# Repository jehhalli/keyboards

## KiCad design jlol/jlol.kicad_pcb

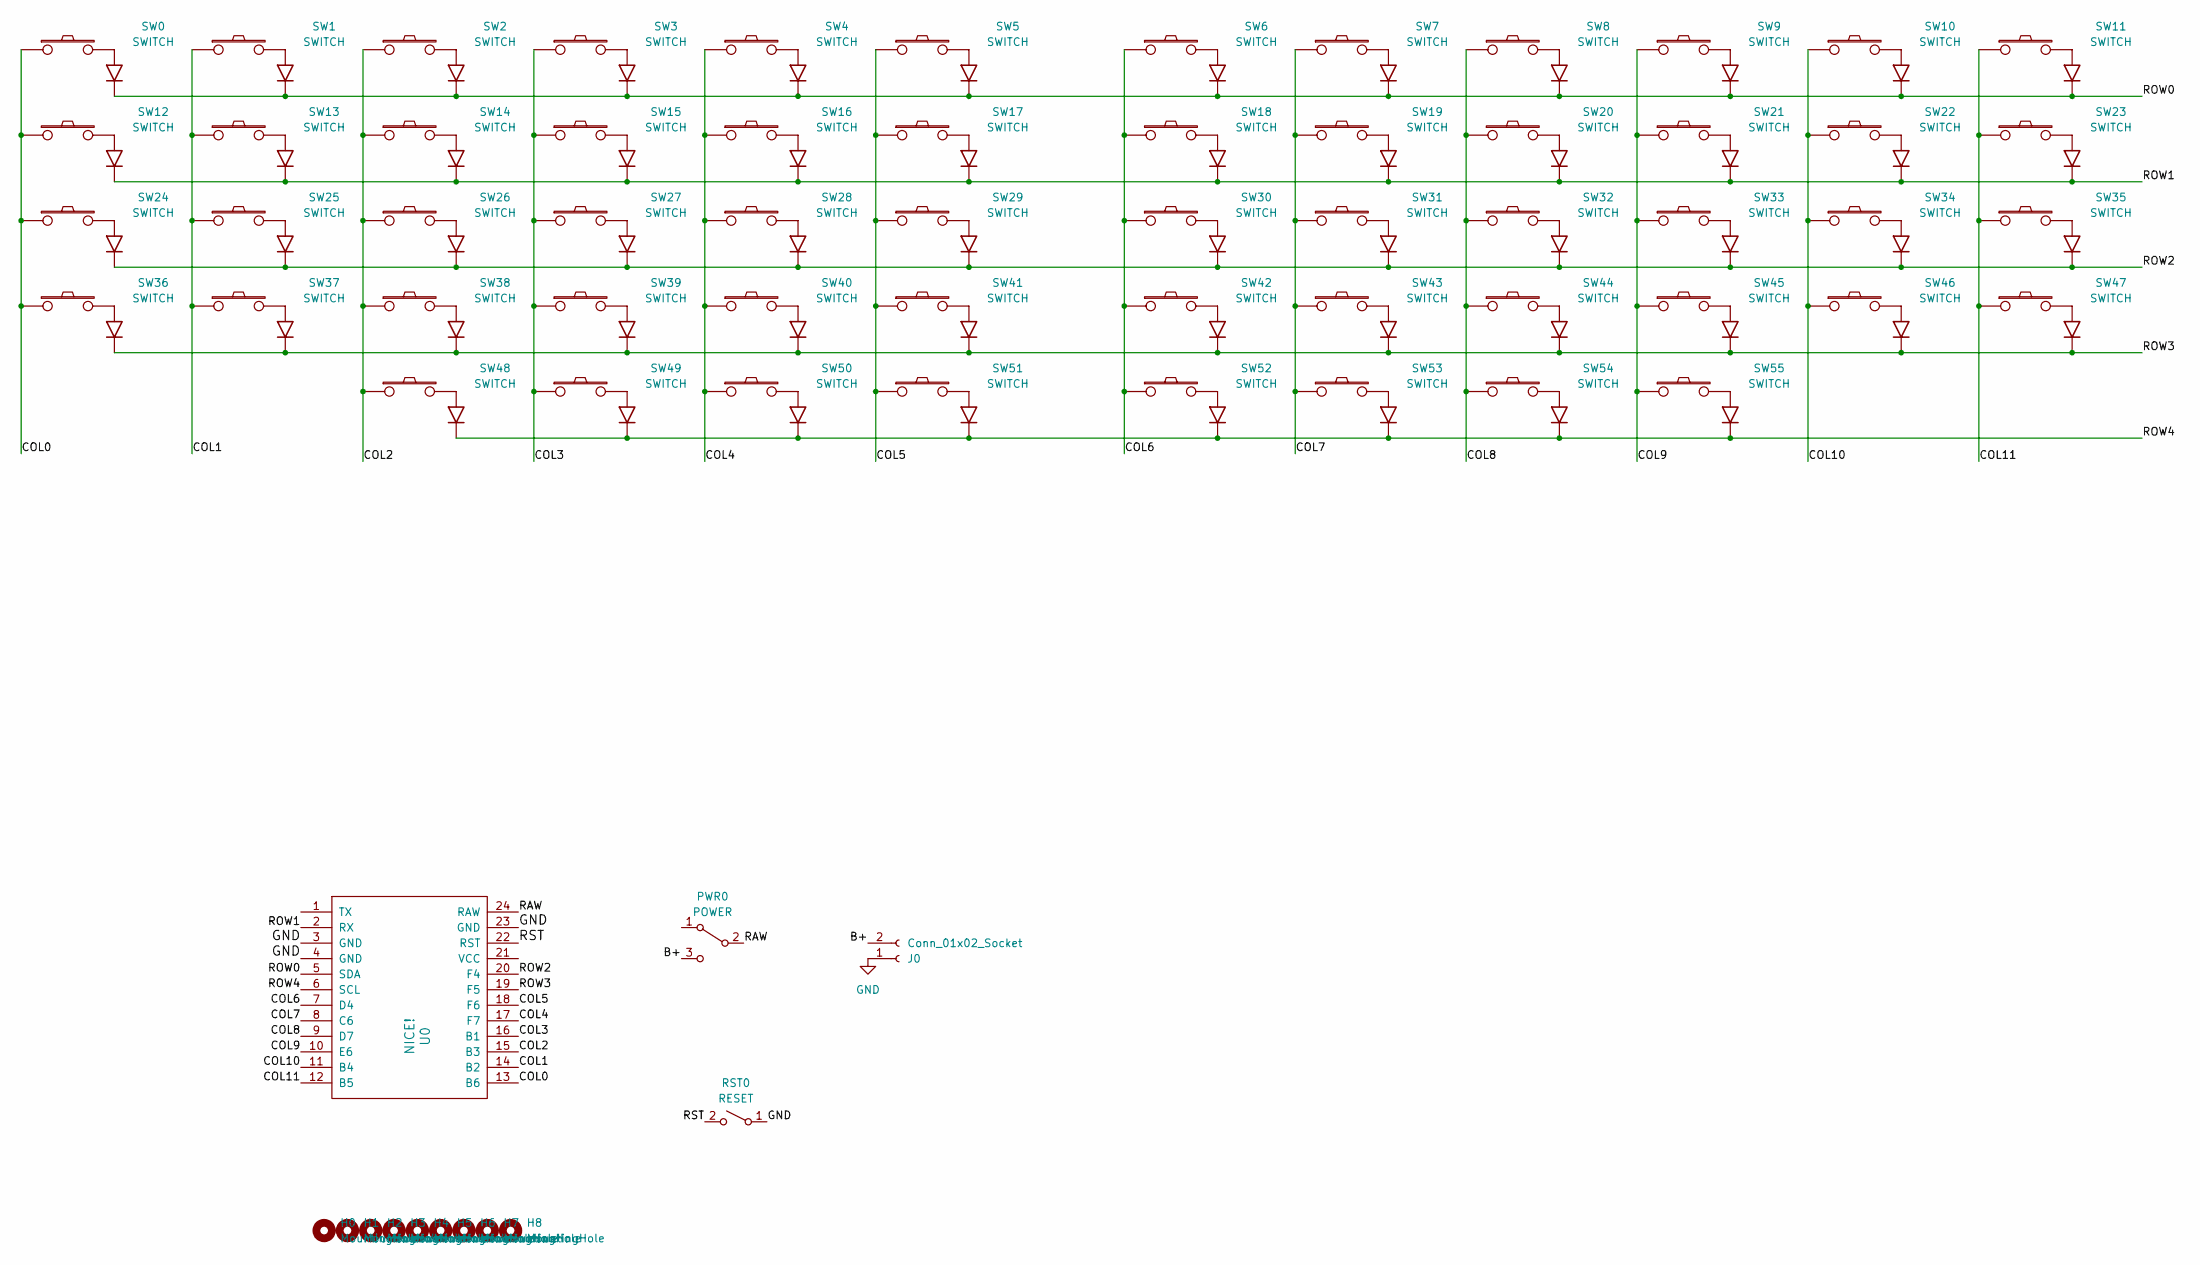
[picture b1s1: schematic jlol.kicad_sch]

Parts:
H0, H1, H2, H3, H4, H5, H6, H7, H8: MountingHole; MountingHole_3.5mm
J0: Conn_01x02_Socket; jst_ph
PWR0: POWER; power_switch_1
RST0: RESET; reset_button
SW0, SW1, SW2, SW3, SW4, SW5, SW6, SW7, SW8, SW9, SW10, SW11, SW12, SW13, SW14, SW15, SW16, SW17, SW18, SW19, SW20, SW21, SW22, SW23, SW24, SW25, SW26, SW27, SW28, SW29, SW30, SW31, SW32, SW33, SW34, SW35, SW36, SW37, SW38, SW39, SW40, SW41, SW42, SW43, SW44, SW45, SW46, SW47, SW48, SW49, SW50, SW51, SW52, SW53, SW54, SW55: SWITCH; cherry_hotswap_with_thru_diode
U0: NICE!; nice!nano

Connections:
/B+: J0.2, PWR0.3 (C)
/COL0: SW0.1, SW12.1, SW24.1, SW36.1, U0.13 (B6)
/COL1: SW1.1, SW13.1, SW25.1, SW37.1, U0.14 (B2)
/COL2: SW2.1, SW14.1, SW26.1, SW38.1, SW48.1, U0.15 (B3)
/COL3: SW3.1, SW15.1, SW27.1, SW39.1, SW49.1, U0.16 (B1)
/COL4: SW4.1, SW16.1, SW28.1, SW40.1, SW50.1, U0.17 (F7)
/COL5: SW5.1, SW17.1, SW29.1, SW41.1, SW51.1, U0.18 (F6)
/COL6: SW6.1, SW18.1, SW30.1, SW42.1, SW52.1, U0.7 (D4)
/COL7: SW7.1, SW19.1, SW31.1, SW43.1, SW53.1, U0.8 (C6)
/COL8: SW8.1, SW20.1, SW32.1, SW44.1, SW54.1, U0.9 (D7)
/COL9: SW9.1, SW21.1, SW33.1, SW45.1, SW55.1, U0.10 (E6)
/COL10: SW10.1, SW22.1, SW34.1, SW46.1, U0.11 (B4)
/COL11: SW11.1, SW23.1, SW35.1, SW47.1, U0.12 (B5)
/RAW: PWR0.2 (B), U0.24 (RAW)
/ROW0: SW0.3 (K), SW1.3 (K), SW2.3 (K), SW3.3 (K), SW4.3 (K), SW5.3 (K), SW6.3 (K), SW7.3 (K), SW8.3 (K), SW9.3 (K), SW10.3 (K), SW11.3 (K), U0.5 (SDA)
/ROW1: SW12.3 (K), SW13.3 (K), SW14.3 (K), SW15.3 (K), SW16.3 (K), SW17.3 (K), SW18.3 (K), SW19.3 (K), SW20.3 (K), SW21.3 (K), SW22.3 (K), SW23.3 (K), U0.2 (RX)
/ROW2: SW24.3 (K), SW25.3 (K), SW26.3 (K), SW27.3 (K), SW28.3 (K), SW29.3 (K), SW30.3 (K), SW31.3 (K), SW32.3 (K), SW33.3 (K), SW34.3 (K), SW35.3 (K), U0.20 (F4)
/ROW3: SW36.3 (K), SW37.3 (K), SW38.3 (K), SW39.3 (K), SW40.3 (K), SW41.3 (K), SW42.3 (K), SW43.3 (K), SW44.3 (K), SW45.3 (K), SW46.3 (K), SW47.3 (K), U0.19 (F5)
/ROW4: SW48.3 (K), SW49.3 (K), SW50.3 (K), SW51.3 (K), SW52.3 (K), SW53.3 (K), SW54.3 (K), SW55.3 (K), U0.6 (SCL)
/RST: RST0.2 (B), U0.22 (RST)
GND: J0.1, RST0.1 (A), U0.3 (GND), U0.4 (GND), U0.23 (GND)

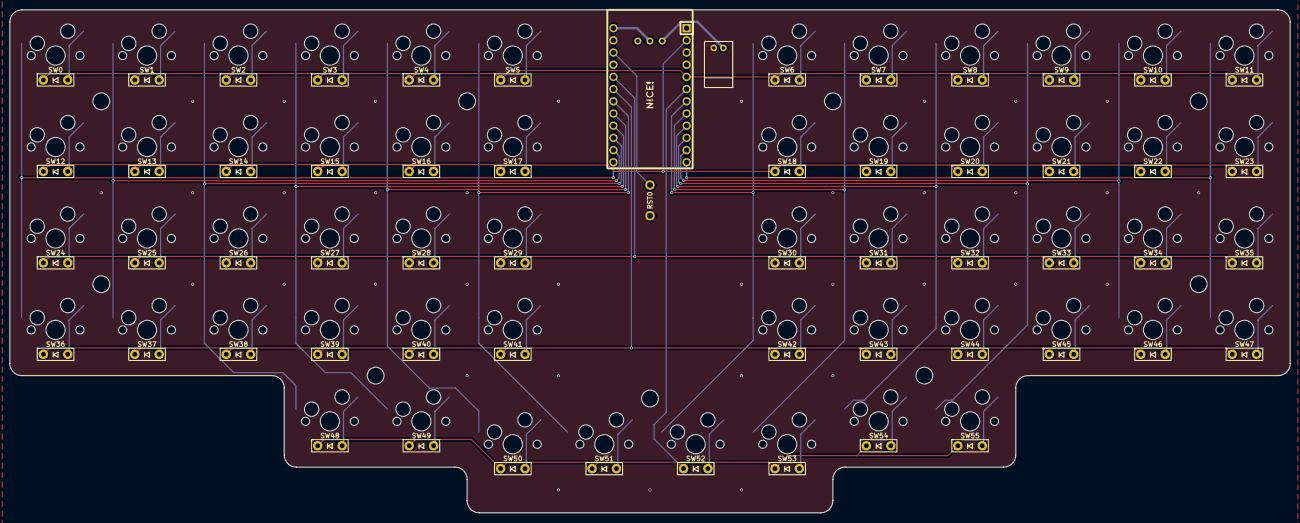
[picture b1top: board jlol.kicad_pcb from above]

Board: 2 copper layers, 266.7 x 104.8 mm, 69 parts (1 on the bottom side), 21 nets.

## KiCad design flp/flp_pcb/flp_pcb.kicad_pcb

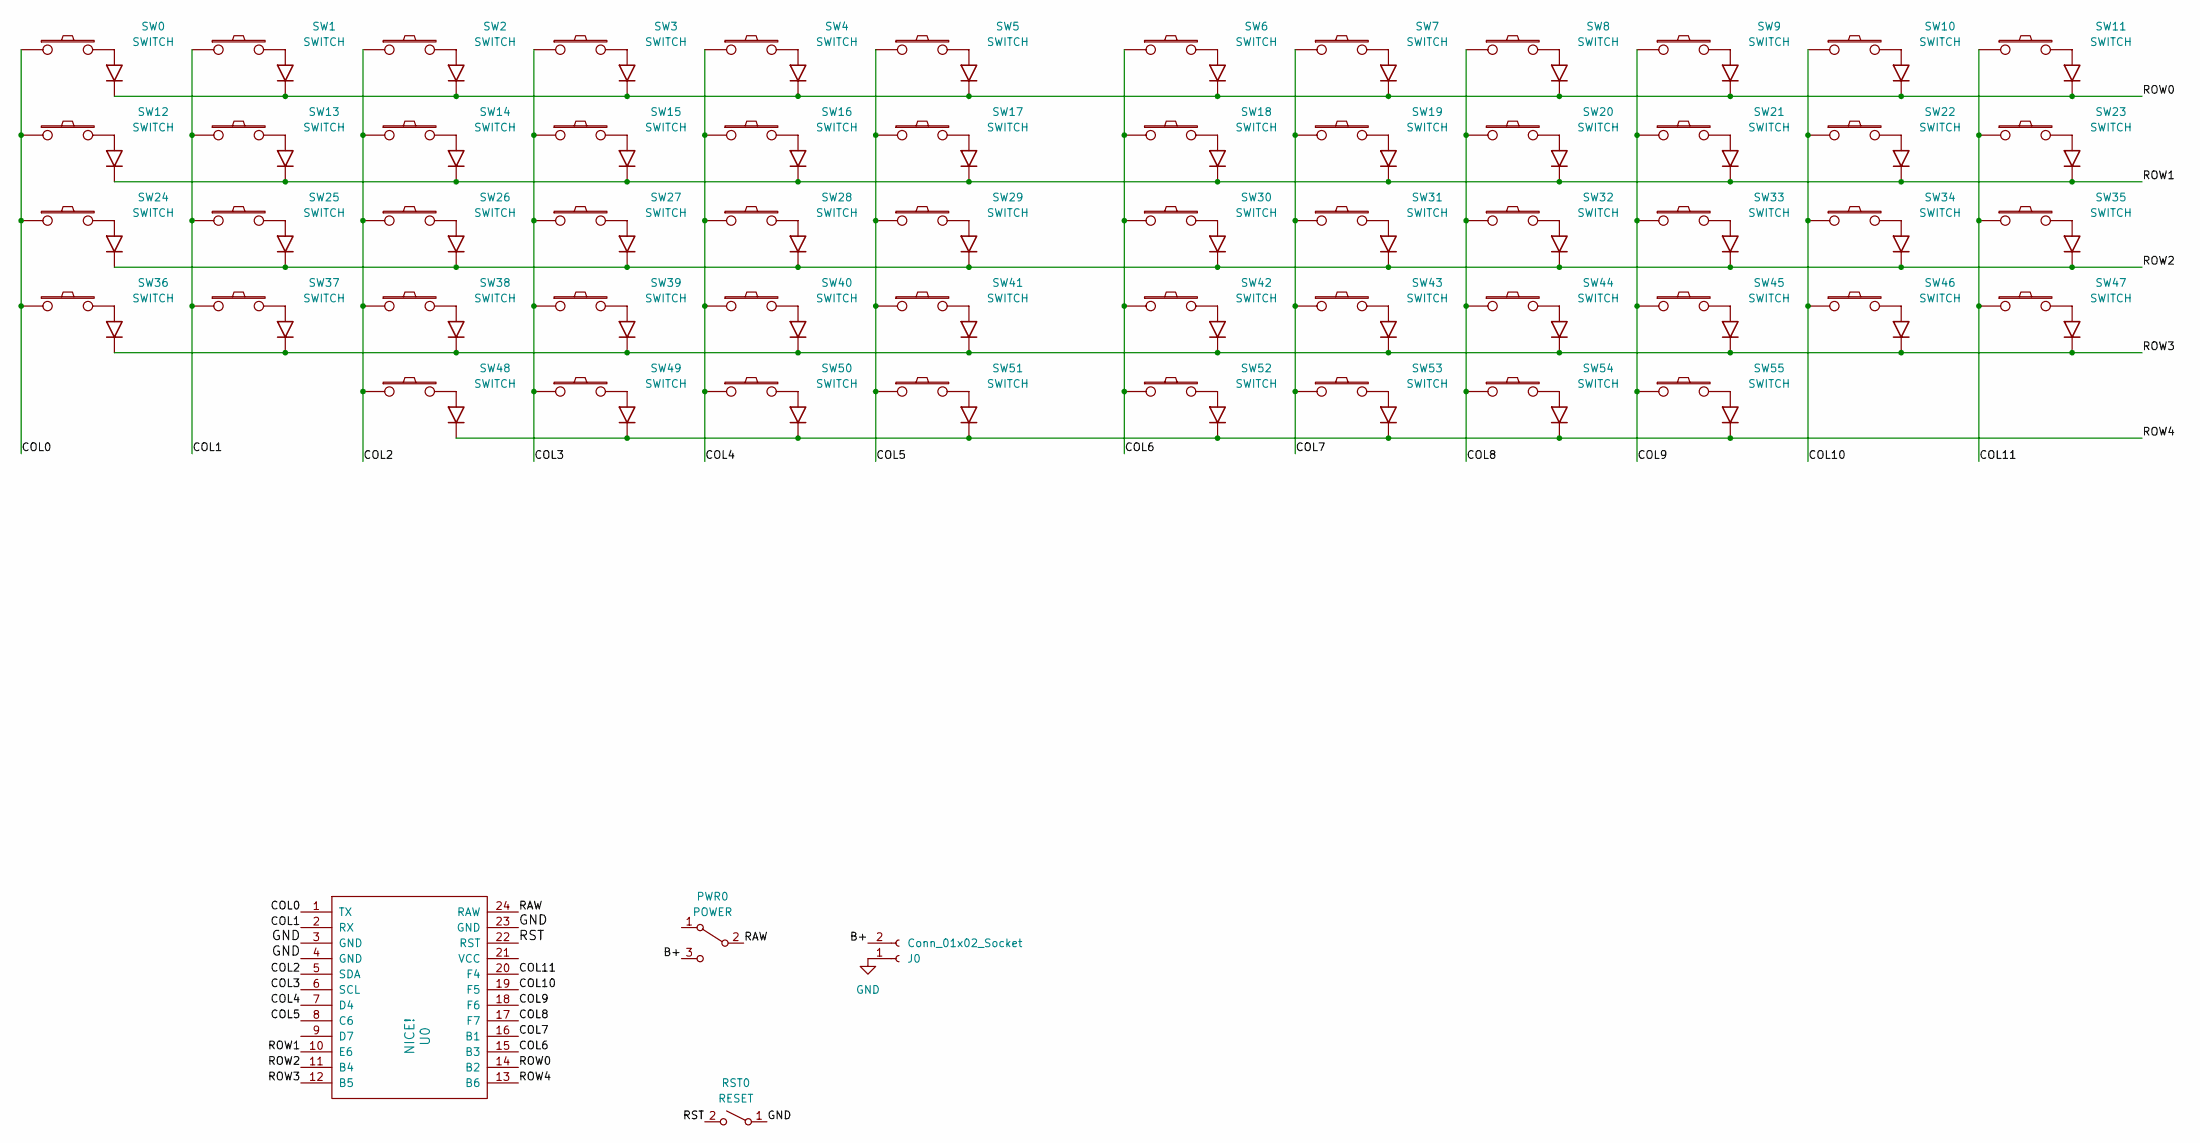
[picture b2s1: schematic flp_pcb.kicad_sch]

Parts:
J0: Conn_01x02_Socket; SolderWire-1sqmm_1x02_P5.4mm_D1.4mm_OD2.7mm
PWR0: POWER; power_switch_1
RST0: RESET; cherry_hotswap
SW0, SW1, SW2, SW3, SW4, SW5, SW6, SW7, SW8, SW9, SW10, SW11, SW12, SW13, SW14, SW15, SW16, SW17, SW18, SW19, SW20, SW21, SW22, SW23, SW24, SW25, SW26, SW27, SW28, SW29, SW30, SW31, SW32, SW33, SW34, SW35, SW36, SW37, SW38, SW39, SW40, SW41, SW42, SW43, SW44, SW45, SW46, SW47, SW48, SW49, SW50, SW51, SW52, SW53, SW54, SW55: SWITCH; kailh_choc_with_diode
U0: NICE!; pro_micro_castellated

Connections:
/B+: J0.2, PWR0.3 (C)
/COL0: SW0.1, SW12.1, SW24.1, SW36.1, U0.1 (TX)
/COL1: SW1.1, SW13.1, SW25.1, SW37.1, U0.2 (RX)
/COL2: SW2.1, SW14.1, SW26.1, SW38.1, SW48.1, U0.5 (SDA)
/COL3: SW3.1, SW15.1, SW27.1, SW39.1, SW49.1, U0.6 (SCL)
/COL4: SW4.1, SW16.1, SW28.1, SW40.1, SW50.1, U0.7 (D4)
/COL5: SW5.1, SW17.1, SW29.1, SW41.1, SW51.1, U0.8 (C6)
/COL6: SW6.1, SW18.1, SW30.1, SW42.1, SW52.1, U0.15 (B3)
/COL7: SW7.1, SW19.1, SW31.1, SW43.1, SW53.1, U0.16 (B1)
/COL8: SW8.1, SW20.1, SW32.1, SW44.1, SW54.1, U0.17 (F7)
/COL9: SW9.1, SW21.1, SW33.1, SW45.1, SW55.1, U0.18 (F6)
/COL10: SW10.1, SW22.1, SW34.1, SW46.1, U0.19 (F5)
/COL11: SW11.1, SW23.1, SW35.1, SW47.1, U0.20 (F4)
/RAW: PWR0.2 (B), U0.24 (RAW)
/ROW0: SW0.3 (K), SW1.3 (K), SW2.3 (K), SW3.3 (K), SW4.3 (K), SW5.3 (K), SW6.3 (K), SW7.3 (K), SW8.3 (K), SW9.3 (K), SW10.3 (K), SW11.3 (K), U0.14 (B2)
/ROW1: SW12.3 (K), SW13.3 (K), SW14.3 (K), SW15.3 (K), SW16.3 (K), SW17.3 (K), SW18.3 (K), SW19.3 (K), SW20.3 (K), SW21.3 (K), SW22.3 (K), SW23.3 (K), U0.10 (E6)
/ROW2: SW24.3 (K), SW25.3 (K), SW26.3 (K), SW27.3 (K), SW28.3 (K), SW29.3 (K), SW30.3 (K), SW31.3 (K), SW32.3 (K), SW33.3 (K), SW34.3 (K), SW35.3 (K), U0.11 (B4)
/ROW3: SW36.3 (K), SW37.3 (K), SW38.3 (K), SW39.3 (K), SW40.3 (K), SW41.3 (K), SW42.3 (K), SW43.3 (K), SW44.3 (K), SW45.3 (K), SW46.3 (K), SW47.3 (K), U0.12 (B5)
/ROW4: SW48.3 (K), SW49.3 (K), SW50.3 (K), SW51.3 (K), SW52.3 (K), SW53.3 (K), SW54.3 (K), SW55.3 (K), U0.13 (B6)
/RST: RST0.2 (B), U0.22 (RST)
GND: J0.1, RST0.1 (A), U0.3 (GND), U0.4 (GND), U0.23 (GND)

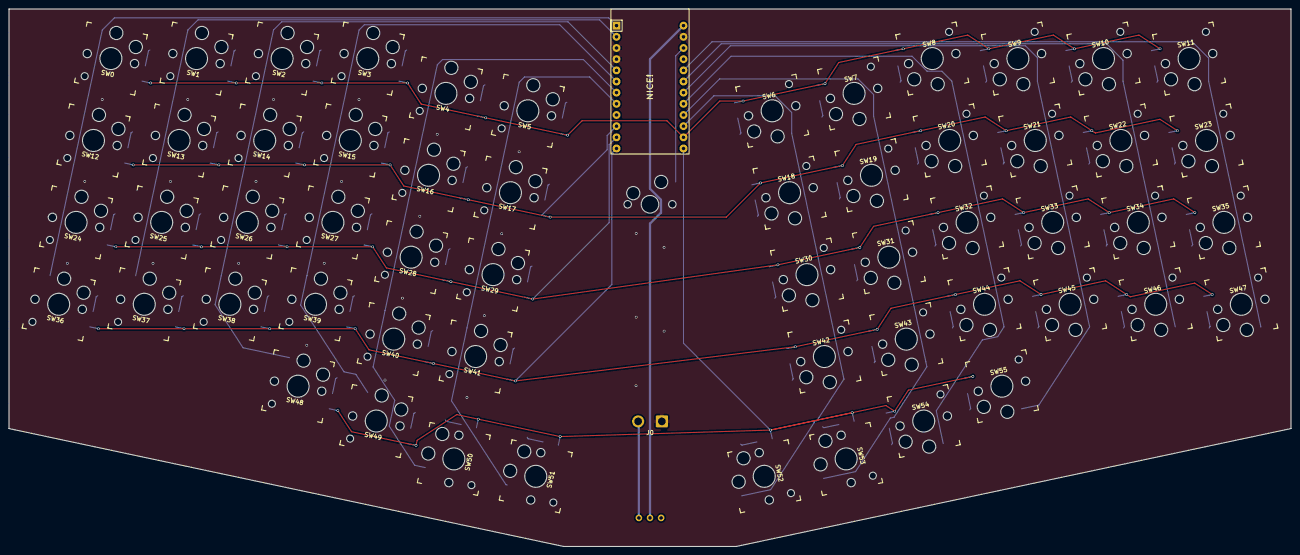
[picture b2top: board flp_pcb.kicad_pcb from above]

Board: 2 copper layers, 291.6 x 122.3 mm, 60 parts (0 on the bottom side), 21 nets.

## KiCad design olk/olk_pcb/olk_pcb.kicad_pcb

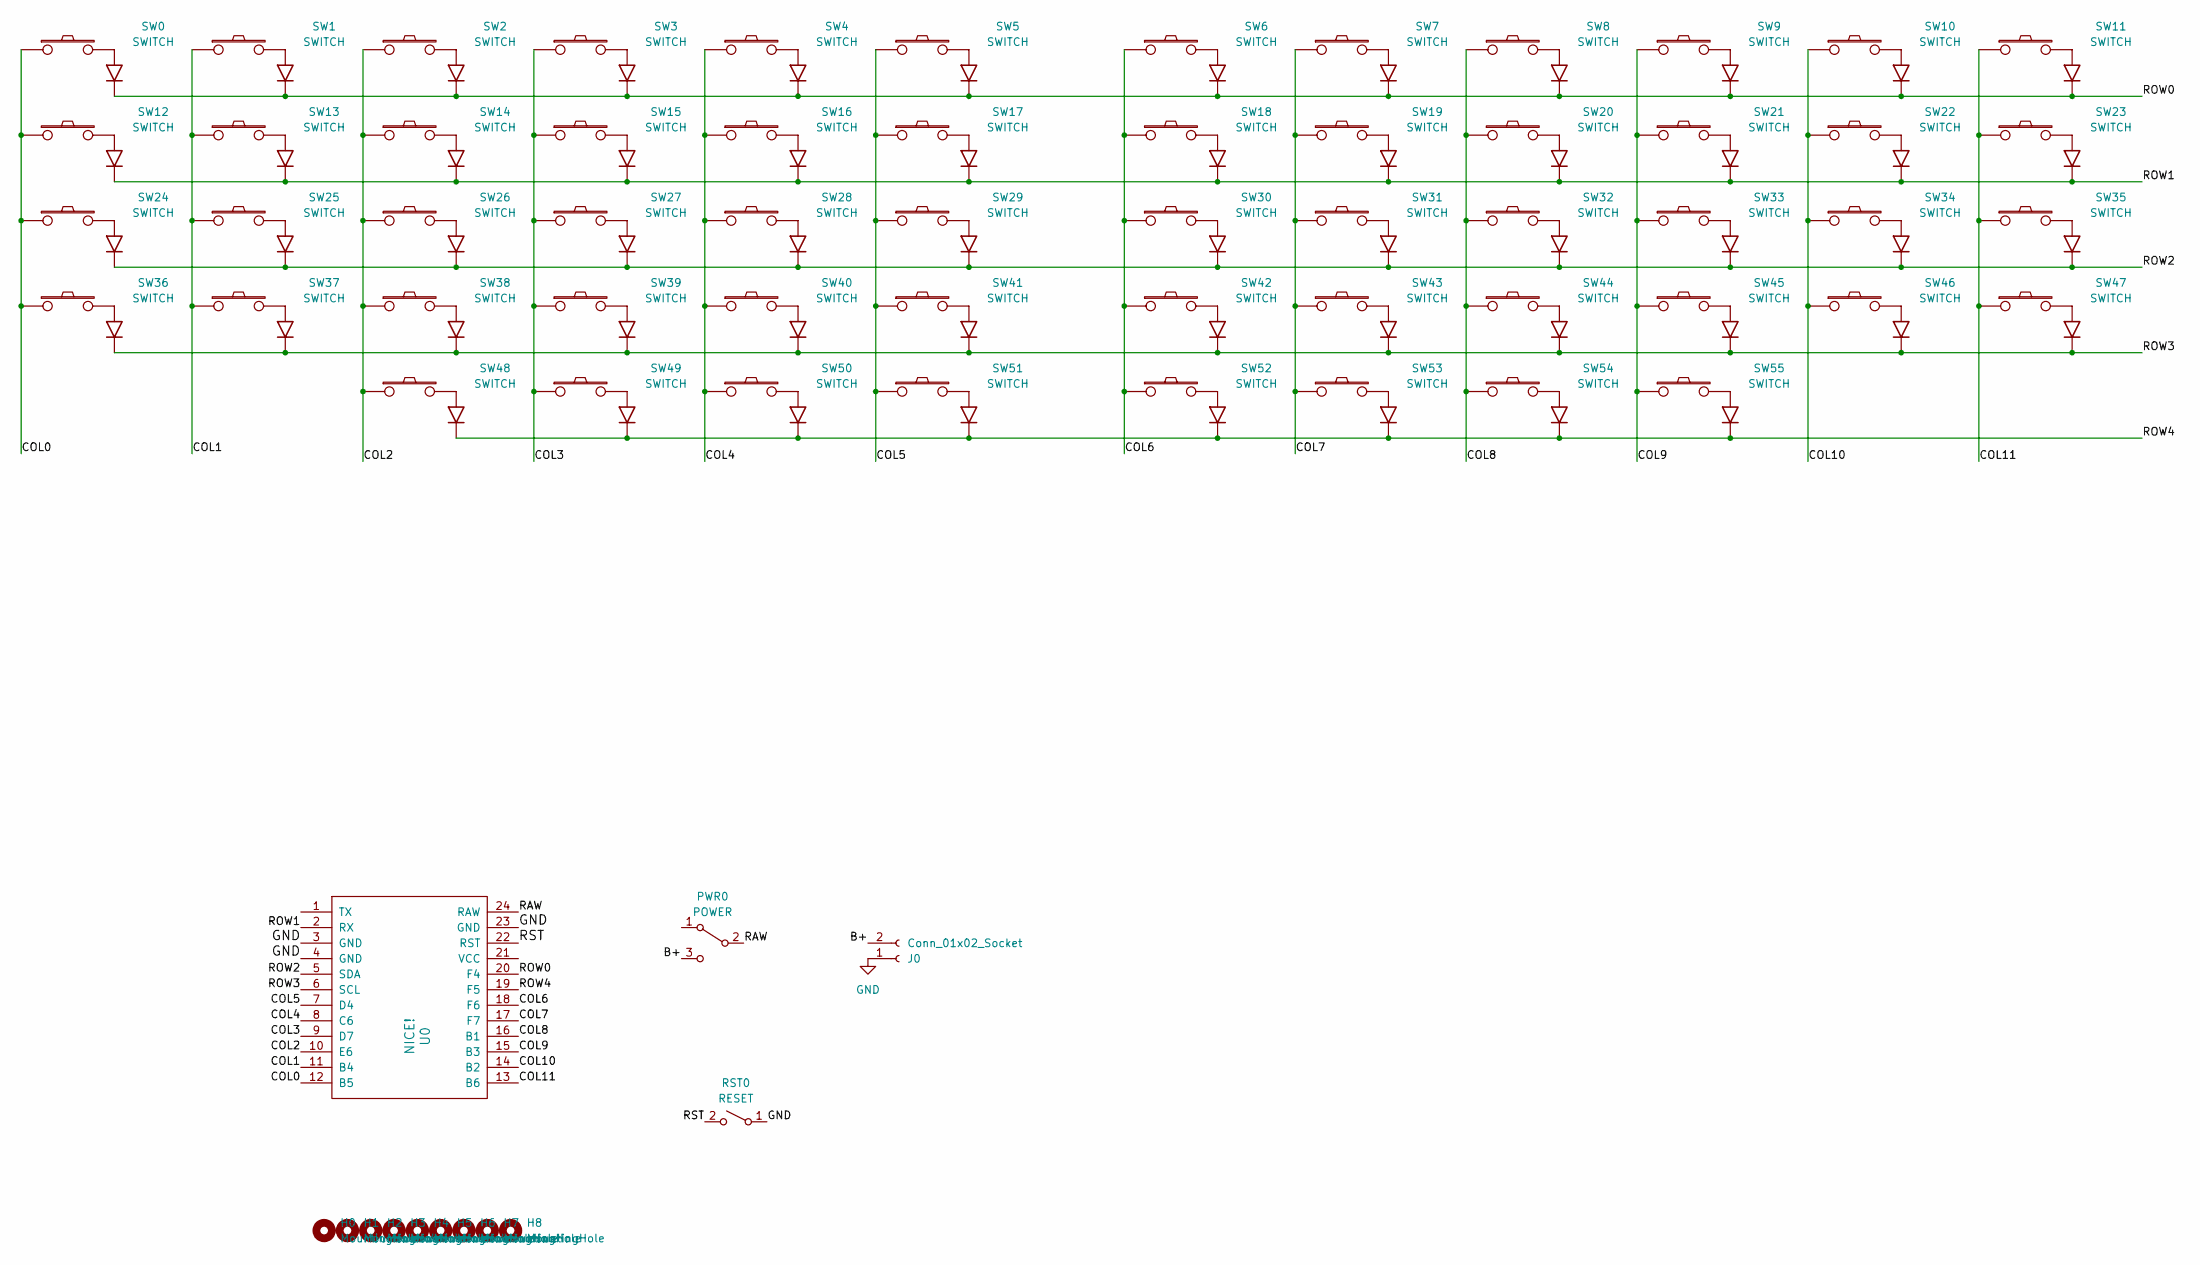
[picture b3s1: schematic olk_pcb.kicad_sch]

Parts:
H0, H1, H2, H3, H4, H5, H6, H7, H8: MountingHole; MountingHole_3.5mm
J0: Conn_01x02_Socket; PinHeader_1x02_P2.54mm_Vertical
PWR0: POWER; power_switch_1
RST0: RESET; reset_button
SW0, SW1, SW2, SW3, SW4, SW5, SW6, SW7, SW8, SW9, SW10, SW11, SW12, SW13, SW14, SW15, SW16, SW17, SW18, SW19, SW20, SW21, SW22, SW23, SW24, SW25, SW26, SW27, SW28, SW29, SW30, SW31, SW32, SW33, SW34, SW35, SW36, SW37, SW38, SW39, SW40, SW41, SW42, SW43, SW44, SW45, SW46, SW47, SW48, SW49, SW50, SW51, SW52, SW53, SW54, SW55: SWITCH; cherry_hotswap_with_diode
U0: NICE!; pro_micro_castellated

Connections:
/B+: J0.2, PWR0.3 (C)
/COL0: SW0.1, SW12.1, SW24.1, SW36.1, U0.12 (B5)
/COL1: SW1.1, SW13.1, SW25.1, SW37.1, U0.11 (B4)
/COL2: SW2.1, SW14.1, SW26.1, SW38.1, SW48.1, U0.10 (E6)
/COL3: SW3.1, SW15.1, SW27.1, SW39.1, SW49.1, U0.9 (D7)
/COL4: SW4.1, SW16.1, SW28.1, SW40.1, SW50.1, U0.8 (C6)
/COL5: SW5.1, SW17.1, SW29.1, SW41.1, SW51.1, U0.7 (D4)
/COL6: SW6.1, SW18.1, SW30.1, SW42.1, SW52.1, U0.18 (F6)
/COL7: SW7.1, SW19.1, SW31.1, SW43.1, SW53.1, U0.17 (F7)
/COL8: SW8.1, SW20.1, SW32.1, SW44.1, SW54.1, U0.16 (B1)
/COL9: SW9.1, SW21.1, SW33.1, SW45.1, SW55.1, U0.15 (B3)
/COL10: SW10.1, SW22.1, SW34.1, SW46.1, U0.14 (B2)
/COL11: SW11.1, SW23.1, SW35.1, SW47.1, U0.13 (B6)
/RAW: PWR0.2 (B), U0.24 (RAW)
/ROW0: SW0.3 (K), SW1.3 (K), SW2.3 (K), SW3.3 (K), SW4.3 (K), SW5.3 (K), SW6.3 (K), SW7.3 (K), SW8.3 (K), SW9.3 (K), SW10.3 (K), SW11.3 (K), U0.20 (F4)
/ROW1: SW12.3 (K), SW13.3 (K), SW14.3 (K), SW15.3 (K), SW16.3 (K), SW17.3 (K), SW18.3 (K), SW19.3 (K), SW20.3 (K), SW21.3 (K), SW22.3 (K), SW23.3 (K), U0.2 (RX)
/ROW2: SW24.3 (K), SW25.3 (K), SW26.3 (K), SW27.3 (K), SW28.3 (K), SW29.3 (K), SW30.3 (K), SW31.3 (K), SW32.3 (K), SW33.3 (K), SW34.3 (K), SW35.3 (K), U0.5 (SDA)
/ROW3: SW36.3 (K), SW37.3 (K), SW38.3 (K), SW39.3 (K), SW40.3 (K), SW41.3 (K), SW42.3 (K), SW43.3 (K), SW44.3 (K), SW45.3 (K), SW46.3 (K), SW47.3 (K), U0.6 (SCL)
/ROW4: SW48.3 (K), SW49.3 (K), SW50.3 (K), SW51.3 (K), SW52.3 (K), SW53.3 (K), SW54.3 (K), SW55.3 (K), U0.19 (F5)
/RST: RST0.2 (B), U0.22 (RST)
GND: J0.1, RST0.1 (A), U0.3 (GND), U0.4 (GND), U0.23 (GND)

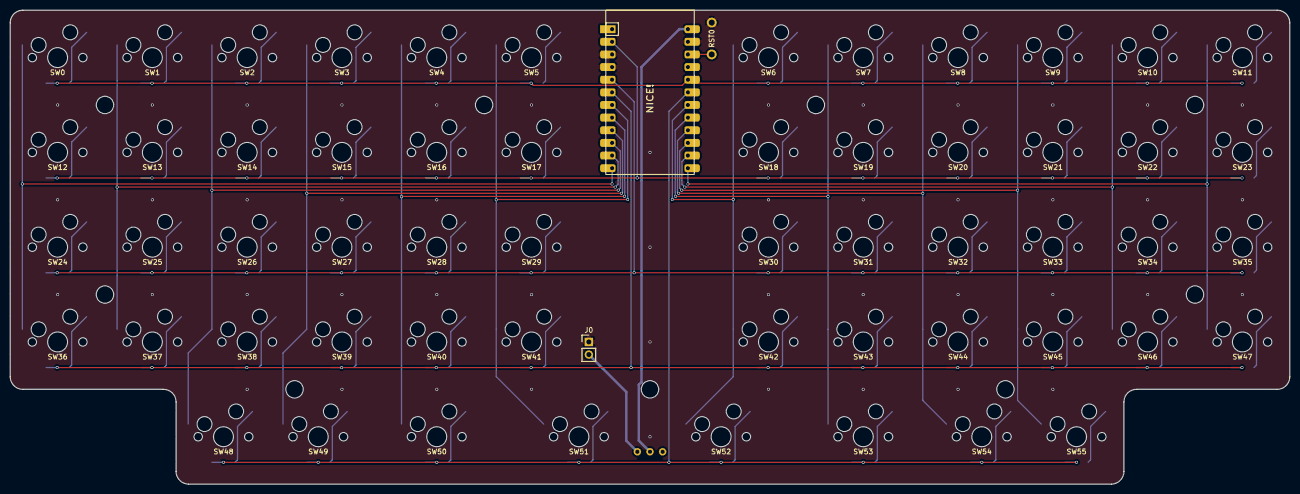
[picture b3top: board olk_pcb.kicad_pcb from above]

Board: 2 copper layers, 257.2 x 95.2 mm, 69 parts (0 on the bottom side), 21 nets.

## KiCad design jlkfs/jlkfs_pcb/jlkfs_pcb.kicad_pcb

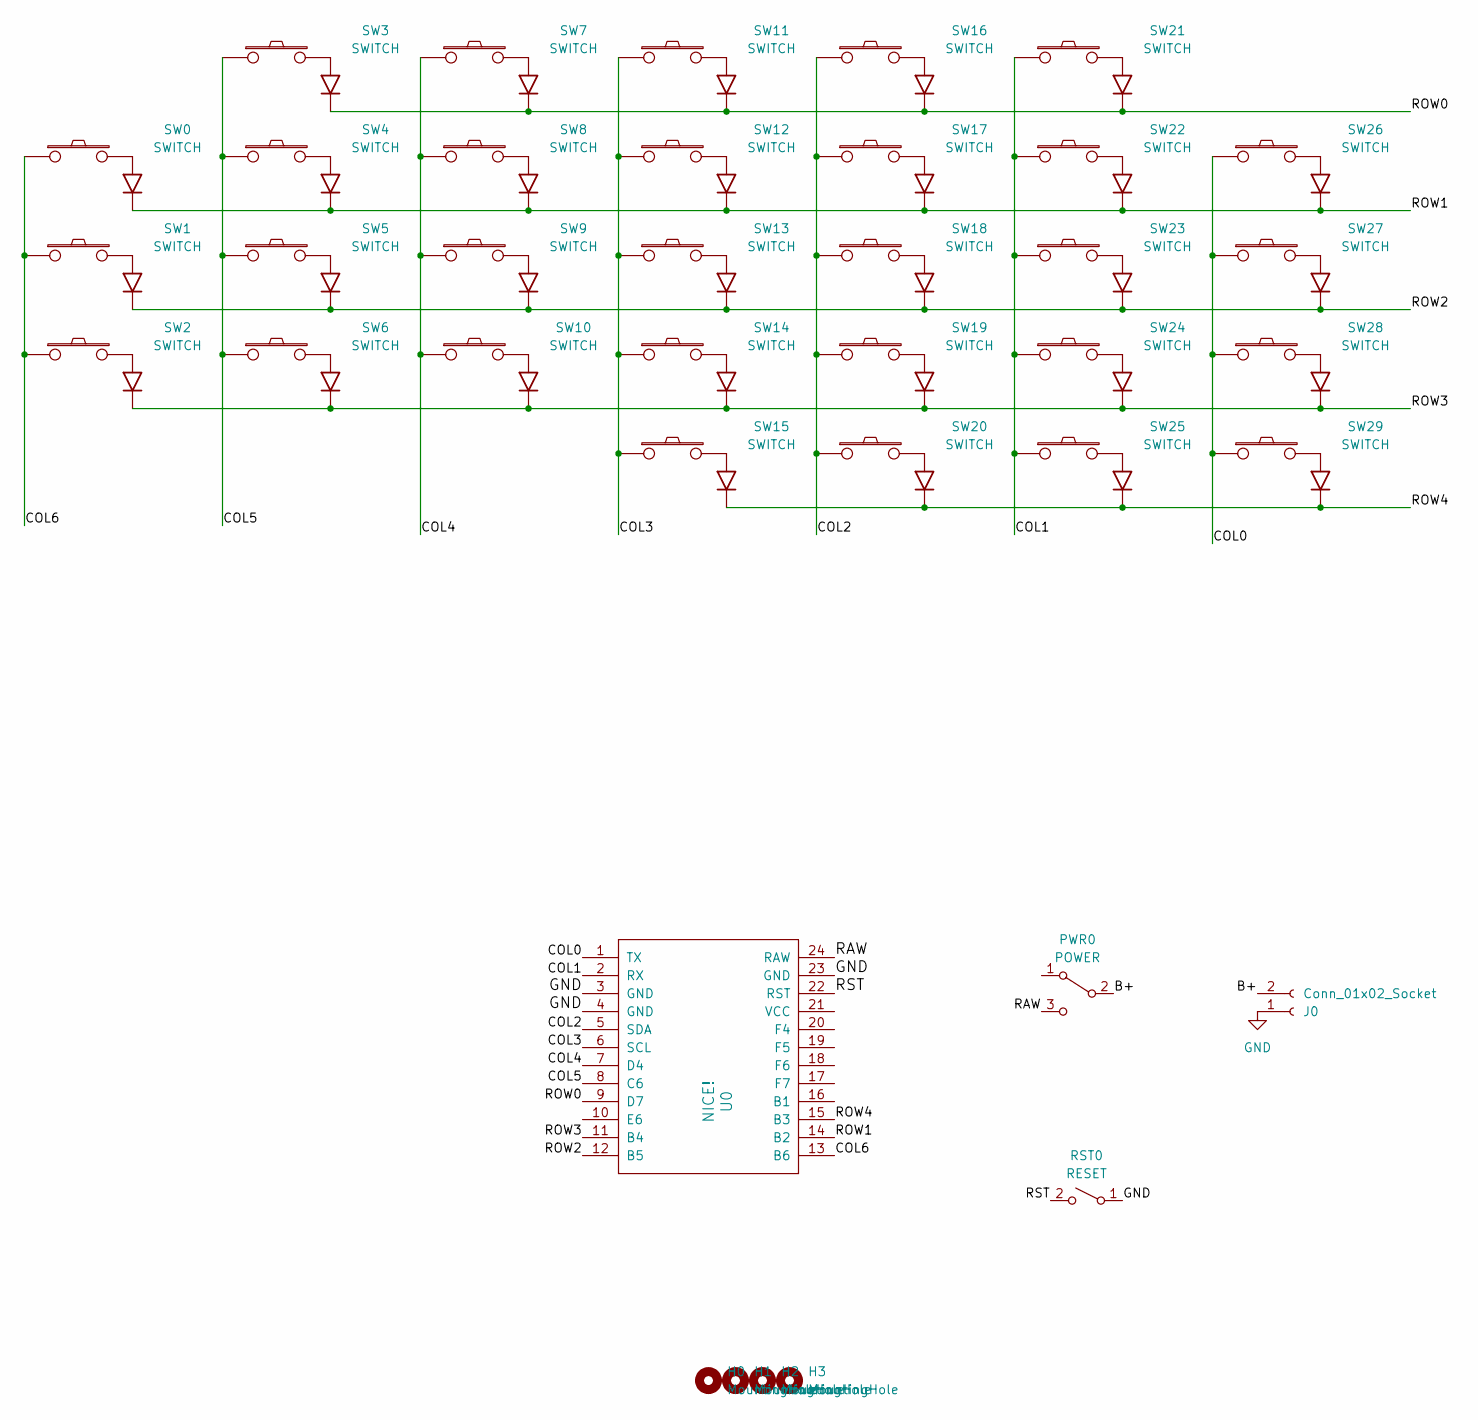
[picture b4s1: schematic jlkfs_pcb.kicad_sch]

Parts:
H0, H1, H2, H3: MountingHole; MountingHole_3.5mm
J0: Conn_01x02_Socket; PinHeader_1x02_P2.54mm_Vertical
PWR0: POWER; power_switch_1
RST0: RESET; reset_button
SW0, SW1, SW2, SW3, SW4, SW5, SW6, SW7, SW8, SW9, SW10, SW11, SW12, SW13, SW14, SW15, SW16, SW17, SW18, SW19, SW20, SW21, SW22, SW23, SW24, SW25, SW26, SW27, SW28, SW29: SWITCH; cherry_hotswap_dual_with_diode
U0: NICE!; nice!nano

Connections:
/B+: J0.2, PWR0.2 (B)
/COL0: SW26.1, SW27.1, SW28.1, SW29.1, U0.1 (TX)
/COL1: SW21.1, SW22.1, SW23.1, SW24.1, SW25.1, U0.2 (RX)
/COL2: SW16.1, SW17.1, SW18.1, SW19.1, SW20.1, U0.5 (SDA)
/COL3: SW11.1, SW12.1, SW13.1, SW14.1, SW15.1, U0.6 (SCL)
/COL4: SW7.1, SW8.1, SW9.1, SW10.1, U0.7 (D4)
/COL5: SW3.1, SW4.1, SW5.1, SW6.1, U0.8 (C6)
/COL6: SW0.1, SW1.1, SW2.1, U0.13 (B6)
/RAW: PWR0.3 (C), U0.24 (RAW)
/ROW0: SW3.3 (K), SW7.3 (K), SW11.3 (K), SW16.3 (K), SW21.3 (K), U0.9 (D7)
/ROW1: SW0.3 (K), SW4.3 (K), SW8.3 (K), SW12.3 (K), SW17.3 (K), SW22.3 (K), SW26.3 (K), U0.14 (B2)
/ROW2: SW1.3 (K), SW5.3 (K), SW9.3 (K), SW13.3 (K), SW18.3 (K), SW23.3 (K), SW27.3 (K), U0.12 (B5)
/ROW3: SW2.3 (K), SW6.3 (K), SW10.3 (K), SW14.3 (K), SW19.3 (K), SW24.3 (K), SW28.3 (K), U0.11 (B4)
/ROW4: SW15.3 (K), SW20.3 (K), SW25.3 (K), SW29.3 (K), U0.15 (B3)
/RST: RST0.2 (B), U0.22 (RST)
GND: J0.1, RST0.1 (A), U0.3 (GND), U0.4 (GND), U0.23 (GND)

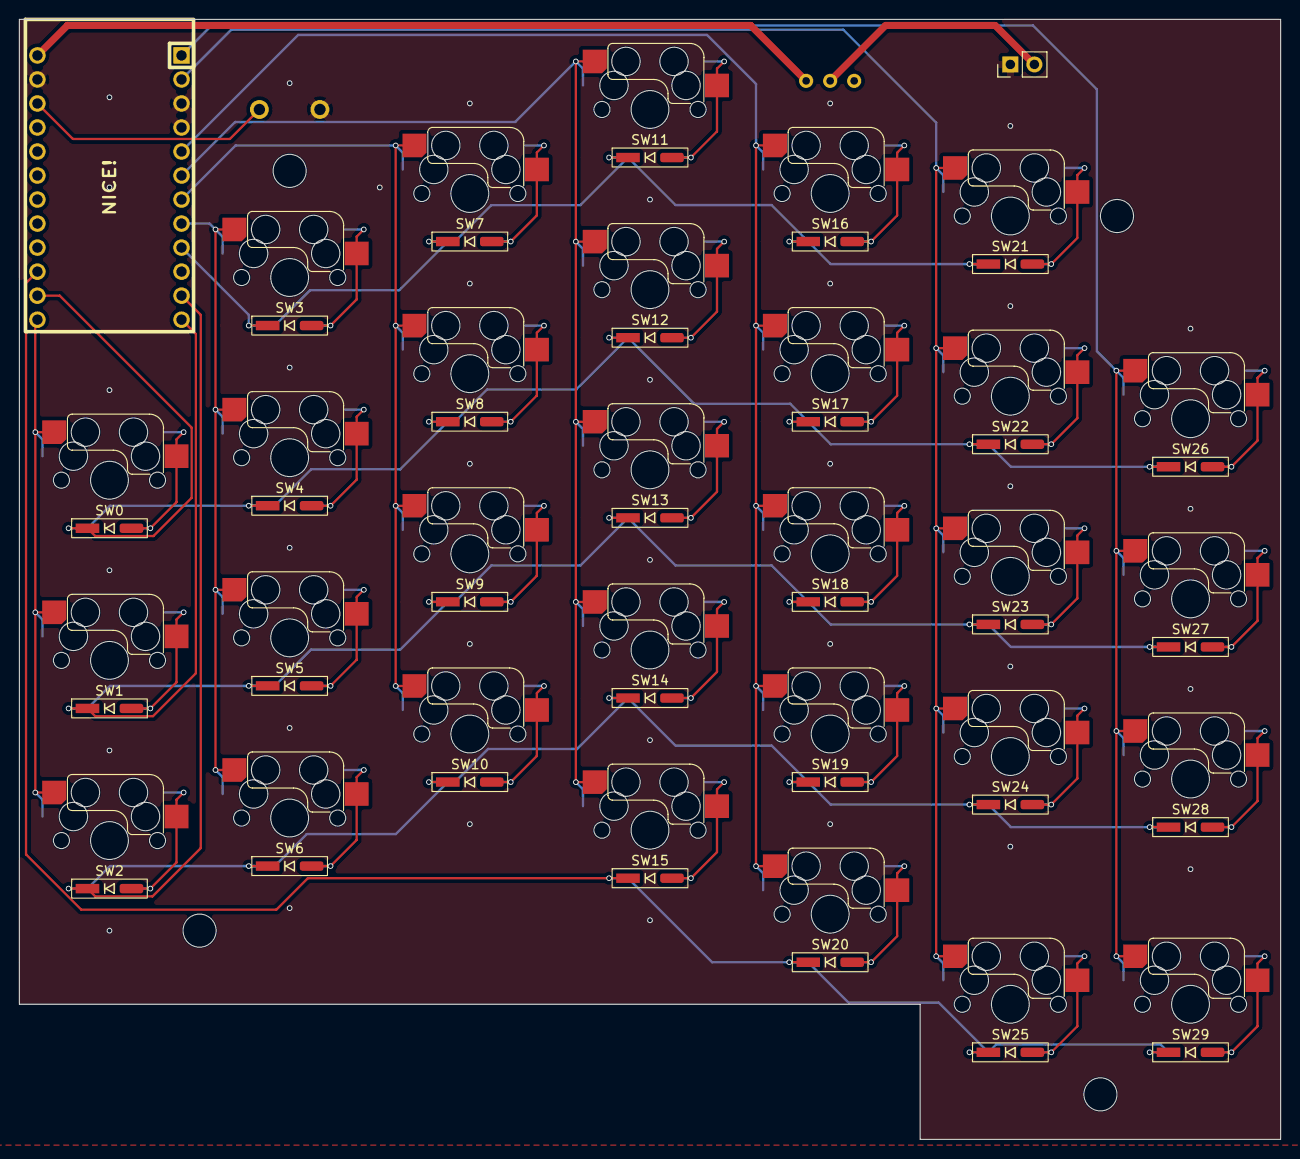
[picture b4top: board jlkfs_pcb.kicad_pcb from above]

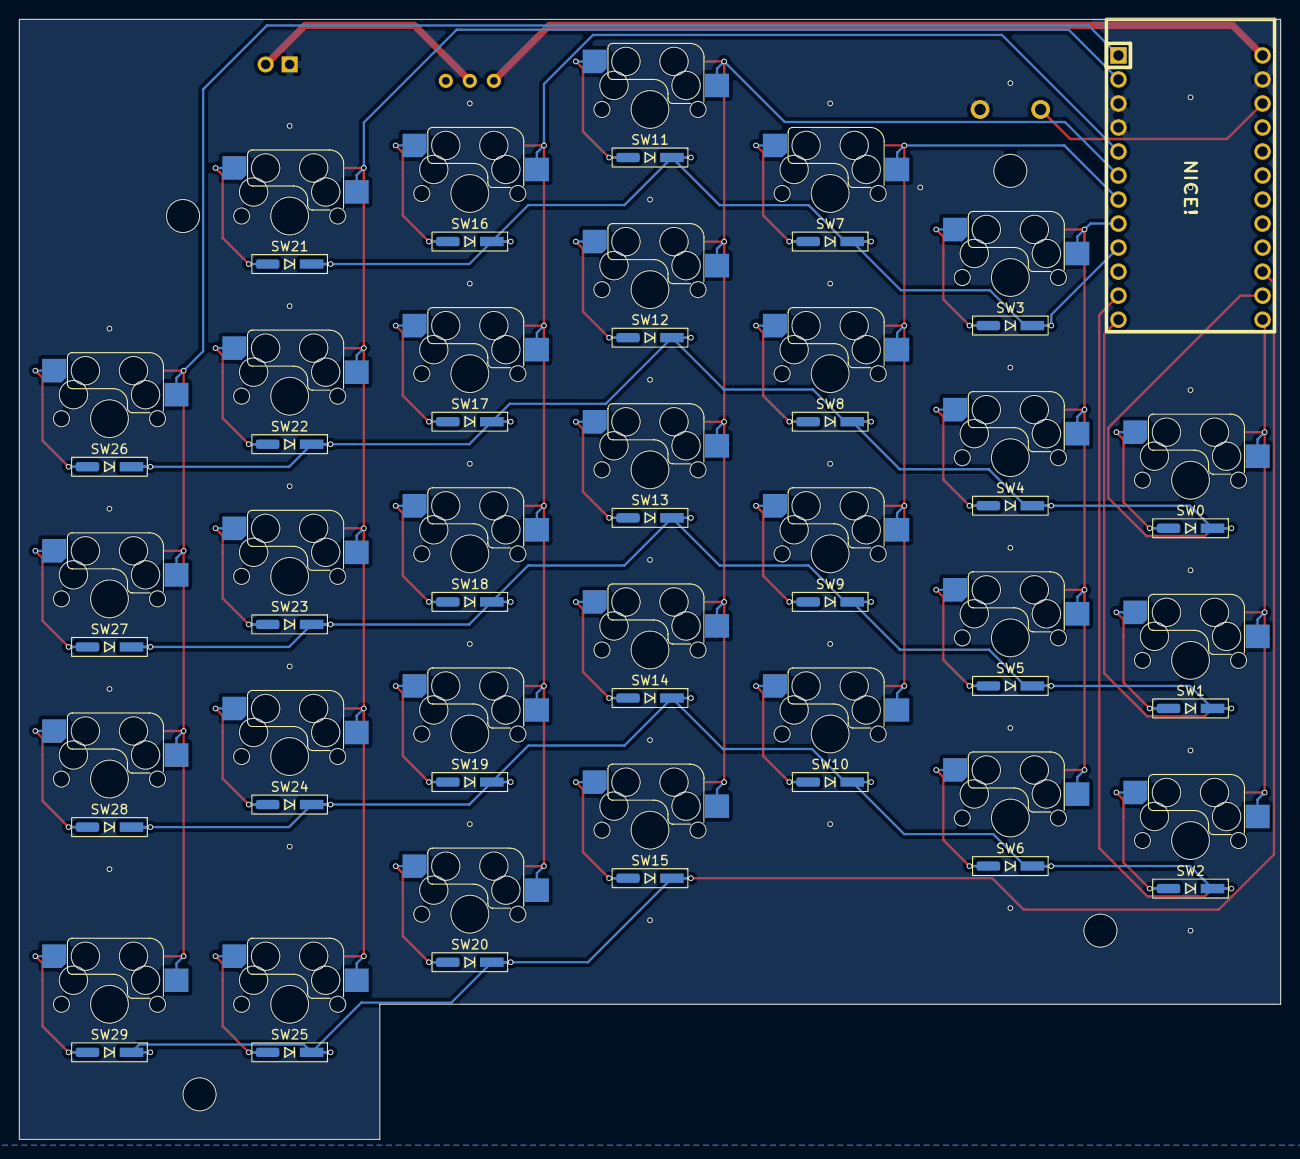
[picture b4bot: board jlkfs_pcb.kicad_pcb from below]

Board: 2 copper layers, 133.3 x 118.4 mm, 38 parts (3 on the bottom side), 16 nets.
